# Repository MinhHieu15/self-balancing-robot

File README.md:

# Self-Balancing Robot

Two-wheeled self-balancing robot, built in two versions:

- **v1**: ESP32 + MPU6050 + DC gear motors, MicroPython, PID tuned on the real robot with Ziegler-Nichols.
- **SBR3**: my redesign of the SBR2.1 main board for a stepper-driven robot. ESP32-S3, two A4988 drivers, MPU-9250 IMU, two MAX7219 LED "eyes", 3S LiPo with soft-start, reverse-polarity and surge protection. Designed in Zener/KiCad, checked with DRC, ERC, SPICE and 269 automated board checks.

|  |  |
|---|---|

## Repository layout
```
v1-micropython/
  firmware/main.py           MPU6050, complementary filter, PID, fall detection
  analysis/nichols.py        ultimate period Tu from logged data, Ziegler-Nichols gains
  analysis/data_compare_angle.py   ITAE of the measured angle per 1 s window
  analysis/*.csv, *.xlsx     tilt angle logged on the robot
sbr3/
  kicad/                     schematic and PCB (KiCad 10)
  gerber/, SBR3_gerber_jlcpcb.zip   fabrication files
  SBR3_BOM.csv, BOM_NOTES.md
  docs/                      schematic PDF, copper plots, 3D renders, DRC report, SPICE results
  zener/                     Zener HDL source, SPICE testbenches, board check script and report
  firmware/sbr3_hw_test/     bring-up test for every block on the board
mechanical/                  robot assembly (STEP) and renders
simulation/                  200 Hz balancing simulation, PID vs LQR
docs/                        plots
```

## v1: PID on the real robot
The tilt angle comes from a complementary filter on the accelerometer angle and the integrated gyro rate:

$$\theta_k = \alpha(\theta_{k-1} + \omega\,\Delta t) + (1-\alpha)\,\theta_{acc}, \quad \alpha = 0.98$$

The PID works on the tilt error with a ±0.2° dead band and a clamped integral. The motors stop past 45° or on an I2C error and restart once the robot is upright.

Tuning started from Ziegler-Nichols. Kp was raised until the robot oscillated steadily at Ku = 120; `nichols.py` finds the peaks in the Teleplot log and gives Tu = 0.671 s, so Kp = 72, Ki = 214.5, Kd = 6.04. Final gains after hand tuning: Kp = 120, Ki = 550, Kd = 0.2.

## SBR3 main board
| Block | Parts |
|---|---|
| MCU | ESP32-S3-DevKitC-1 |
| Motors | 2 × A4988, 1/16 microstepping, shared enable |
| IMU | GY-9250 (MPU-9250) on I2C, interrupt line |
| Eyes | 2 × MAX7219 8×8 modules through a 74AHCT125 level shifter |
| Power | XT30, PTC fuse, AO3401A reverse-polarity FET + soft-start FET, SMBJ15A TVS, MP1584EN buck to 5 V, battery voltage divider to ADC |
| UI | buzzer, button, power and status LEDs |

Power-on inrush was 46 A in simulation before the soft-start was added and 0.91 A after. All SPICE results are in [sbr3/docs/spice_results.md](sbr3/docs/spice_results.md); KiCad DRC reports 0 violations and 0 unconnected items, and [the board check report](sbr3/zener/tests/REPORT.md) lists 269 passing checks (netlist match, track widths, clearances, part ratings, fit inside the robot shell).

| Top | Bottom |
|---|---|
|  |  |

`sbr3/firmware/sbr3_hw_test` tests each block from a serial menu (LED, buzzer, button, battery ADC, IMU WHO_AM_I and readings, eye displays, each motor) and prints a PASS/FAIL summary.

## Simulation: PID vs LQR on SBR3
Steppers set wheel acceleration directly, so the model is a wheeled inverted pendulum with wheel acceleration as input. The loop runs at 200 Hz on a complementary-filter angle estimate from a noisy accelerometer and a biased gyro, with one sample of delay and the stepper's acceleration and speed limits. Logs are in `simulation/results/`.

```bash
pip install numpy scipy matplotlib
cd simulation && python balance_sim.py
```

| Scenario | Controller | ITAE | Max tilt | Settling (±1°) | Final position offset |
|---|---|---|---|---|---|
| 10° initial tilt | PID | 0.053 | 10.0° | 0.46 s | 18.6 cm, still drifting |
| 10° initial tilt | LQR | 0.072 | 10.0° | 0.88 s | 6.0 cm |
| Push, +60°/s | PID | 0.061 | 1.2° | 0.04 s | 8.3 cm |
| Push, +60°/s | LQR | 0.081 | 1.3° | 0.46 s | 6.0 cm |

PID brings the angle back faster, but it has no position feedback beyond a weak speed term, so the robot keeps rolling. LQR is slower on the angle and holds position. The remaining 6 cm offset comes from the gyro bias leaking into the angle estimate.

Both controllers barely change up to 20 ms of delay. PID falls at 35 ms; LQR still balances at 40 ms.

The angle estimate is best around α = 0.96–0.98. Lower α lets accelerometer noise through, higher α lets the gyro bias drift in.

## Credits
- **Robot model.** `mechanical/robot_assembly.step` is "Self-Balancing Robot" by [Mr Robonyx](https://grabcad.com/mr.robonyx-1), downloaded from [GrabCAD](https://grabcad.com/library/self-balancing-robot-13) (uploaded 17 February 2025, [video](https://youtu.be/UwOCjUQFoeM)). It is not my design and is included unchanged; the renders in `mechanical/` are made from it with `render_step.py`. Use of the file is subject to the [GrabCAD terms of use](https://grabcad.com/terms).
- **SBR2.1 board.** SBR3 is a redesign of the SBR2.1 main board by H.M. Phan (Robonyx); the SBR3 board was laid out to fit inside the robot model above.

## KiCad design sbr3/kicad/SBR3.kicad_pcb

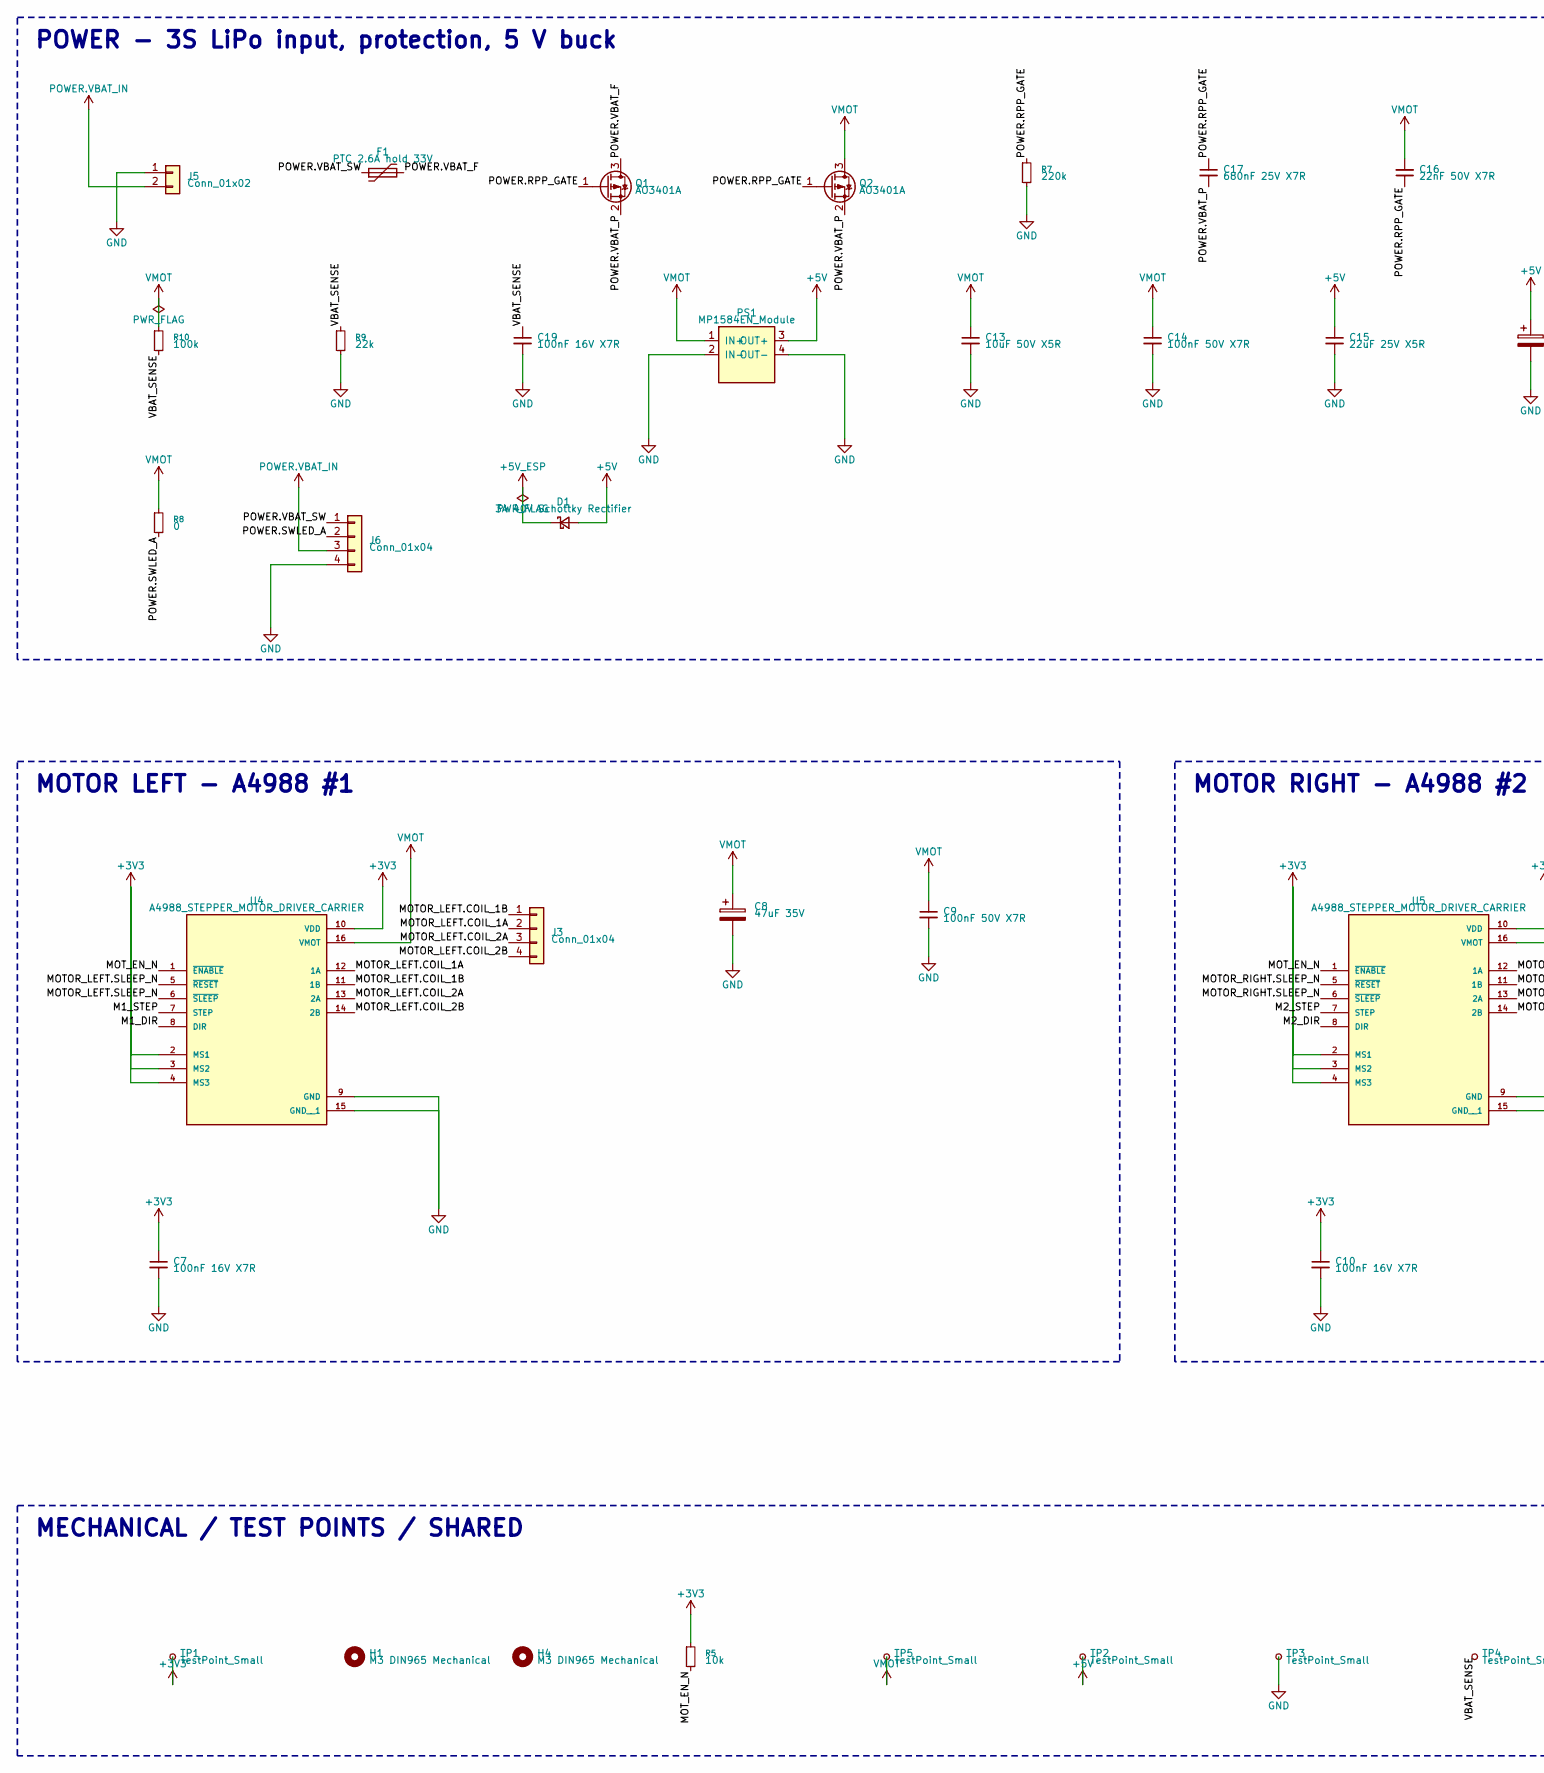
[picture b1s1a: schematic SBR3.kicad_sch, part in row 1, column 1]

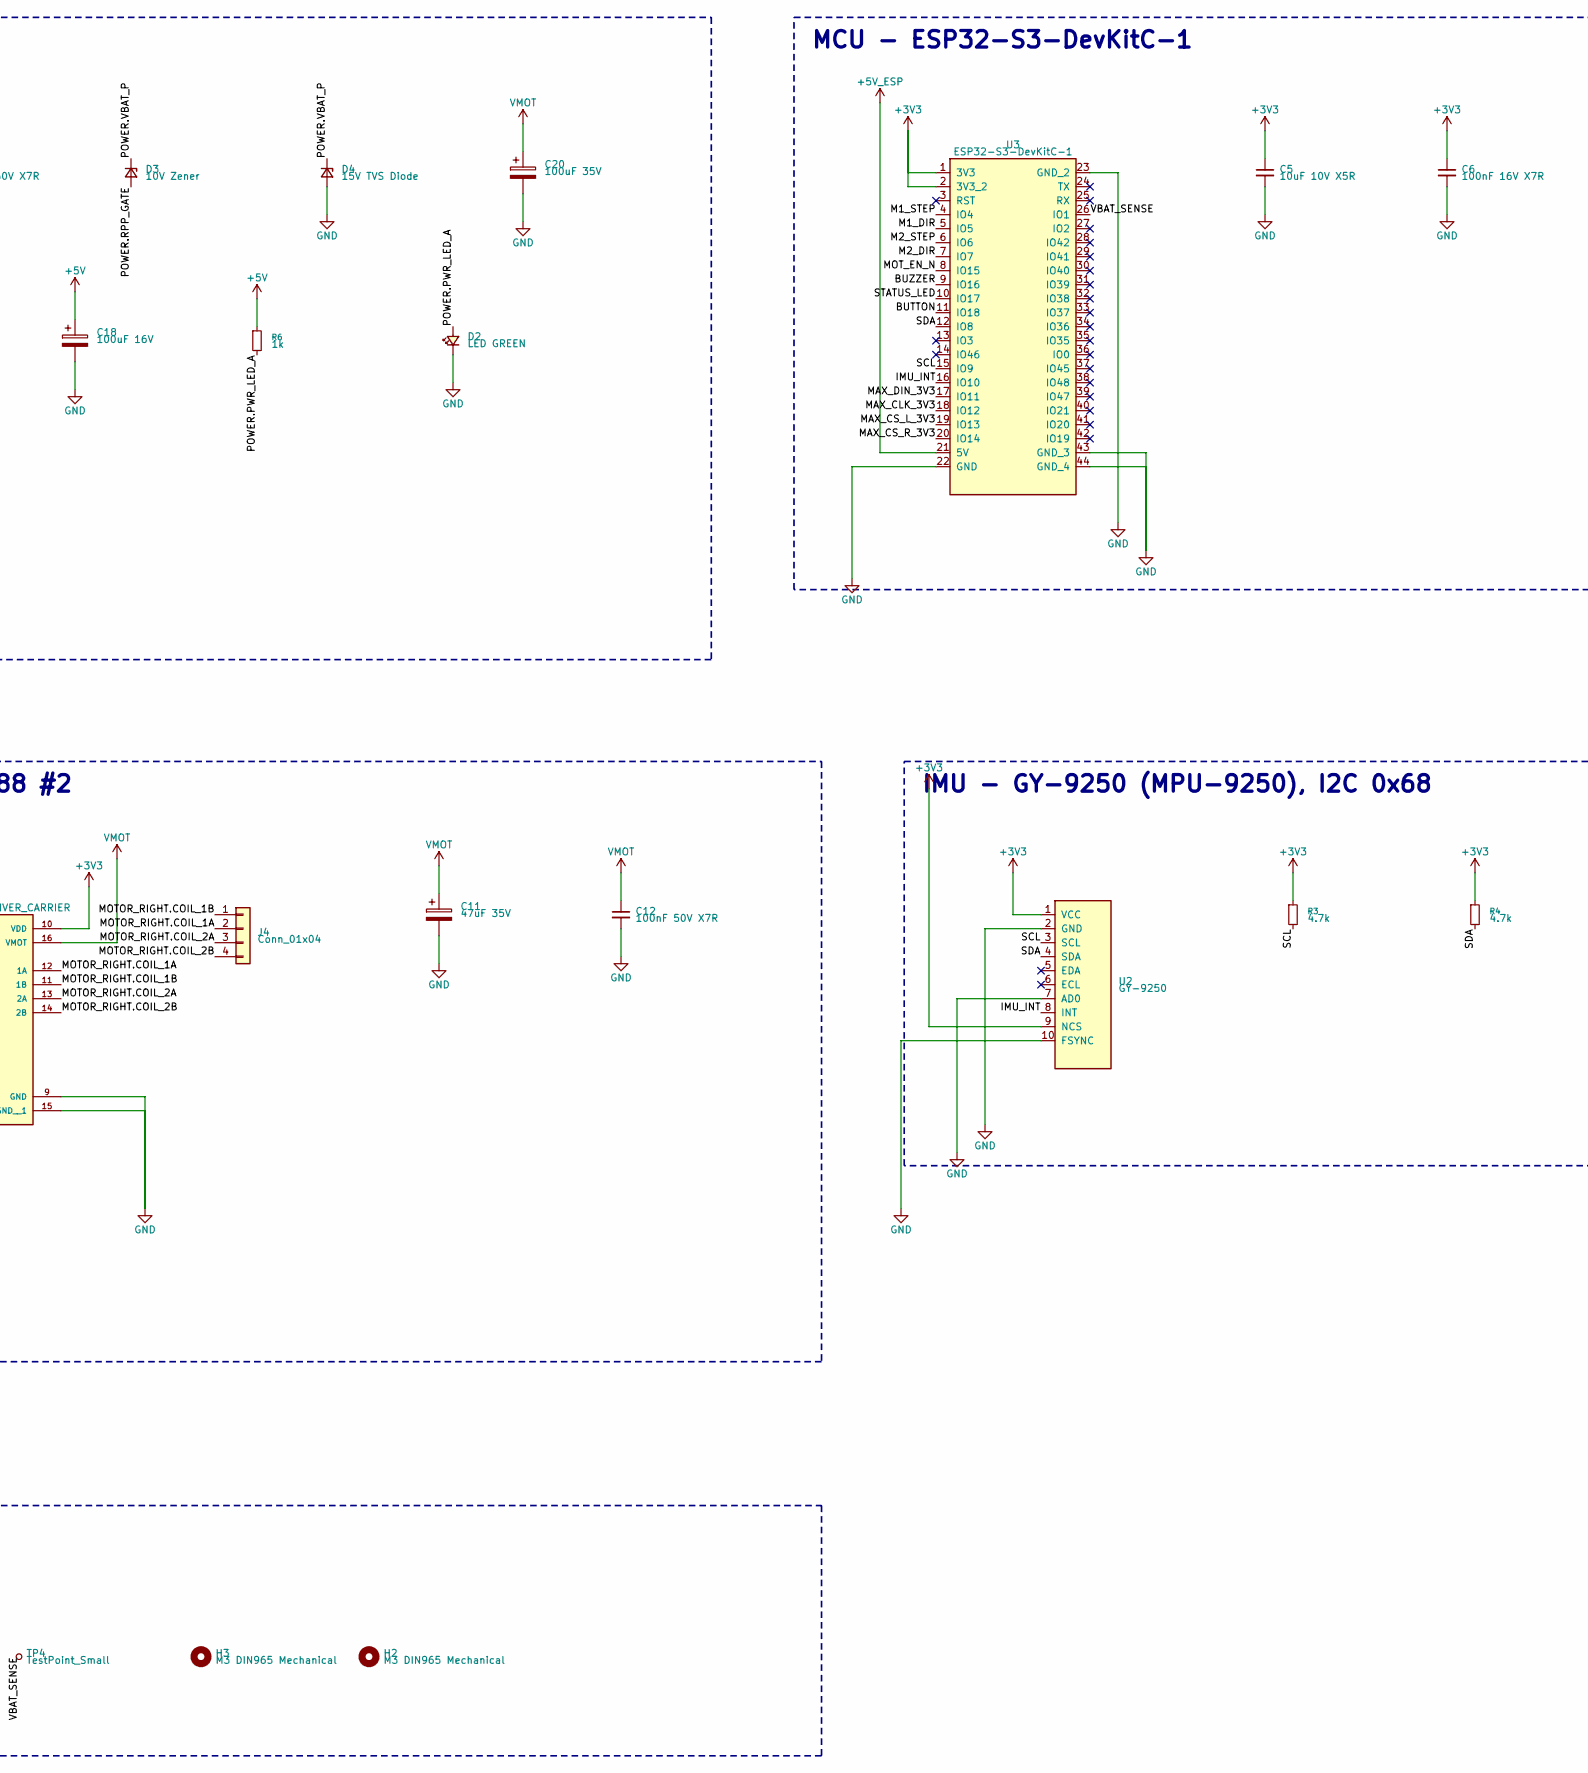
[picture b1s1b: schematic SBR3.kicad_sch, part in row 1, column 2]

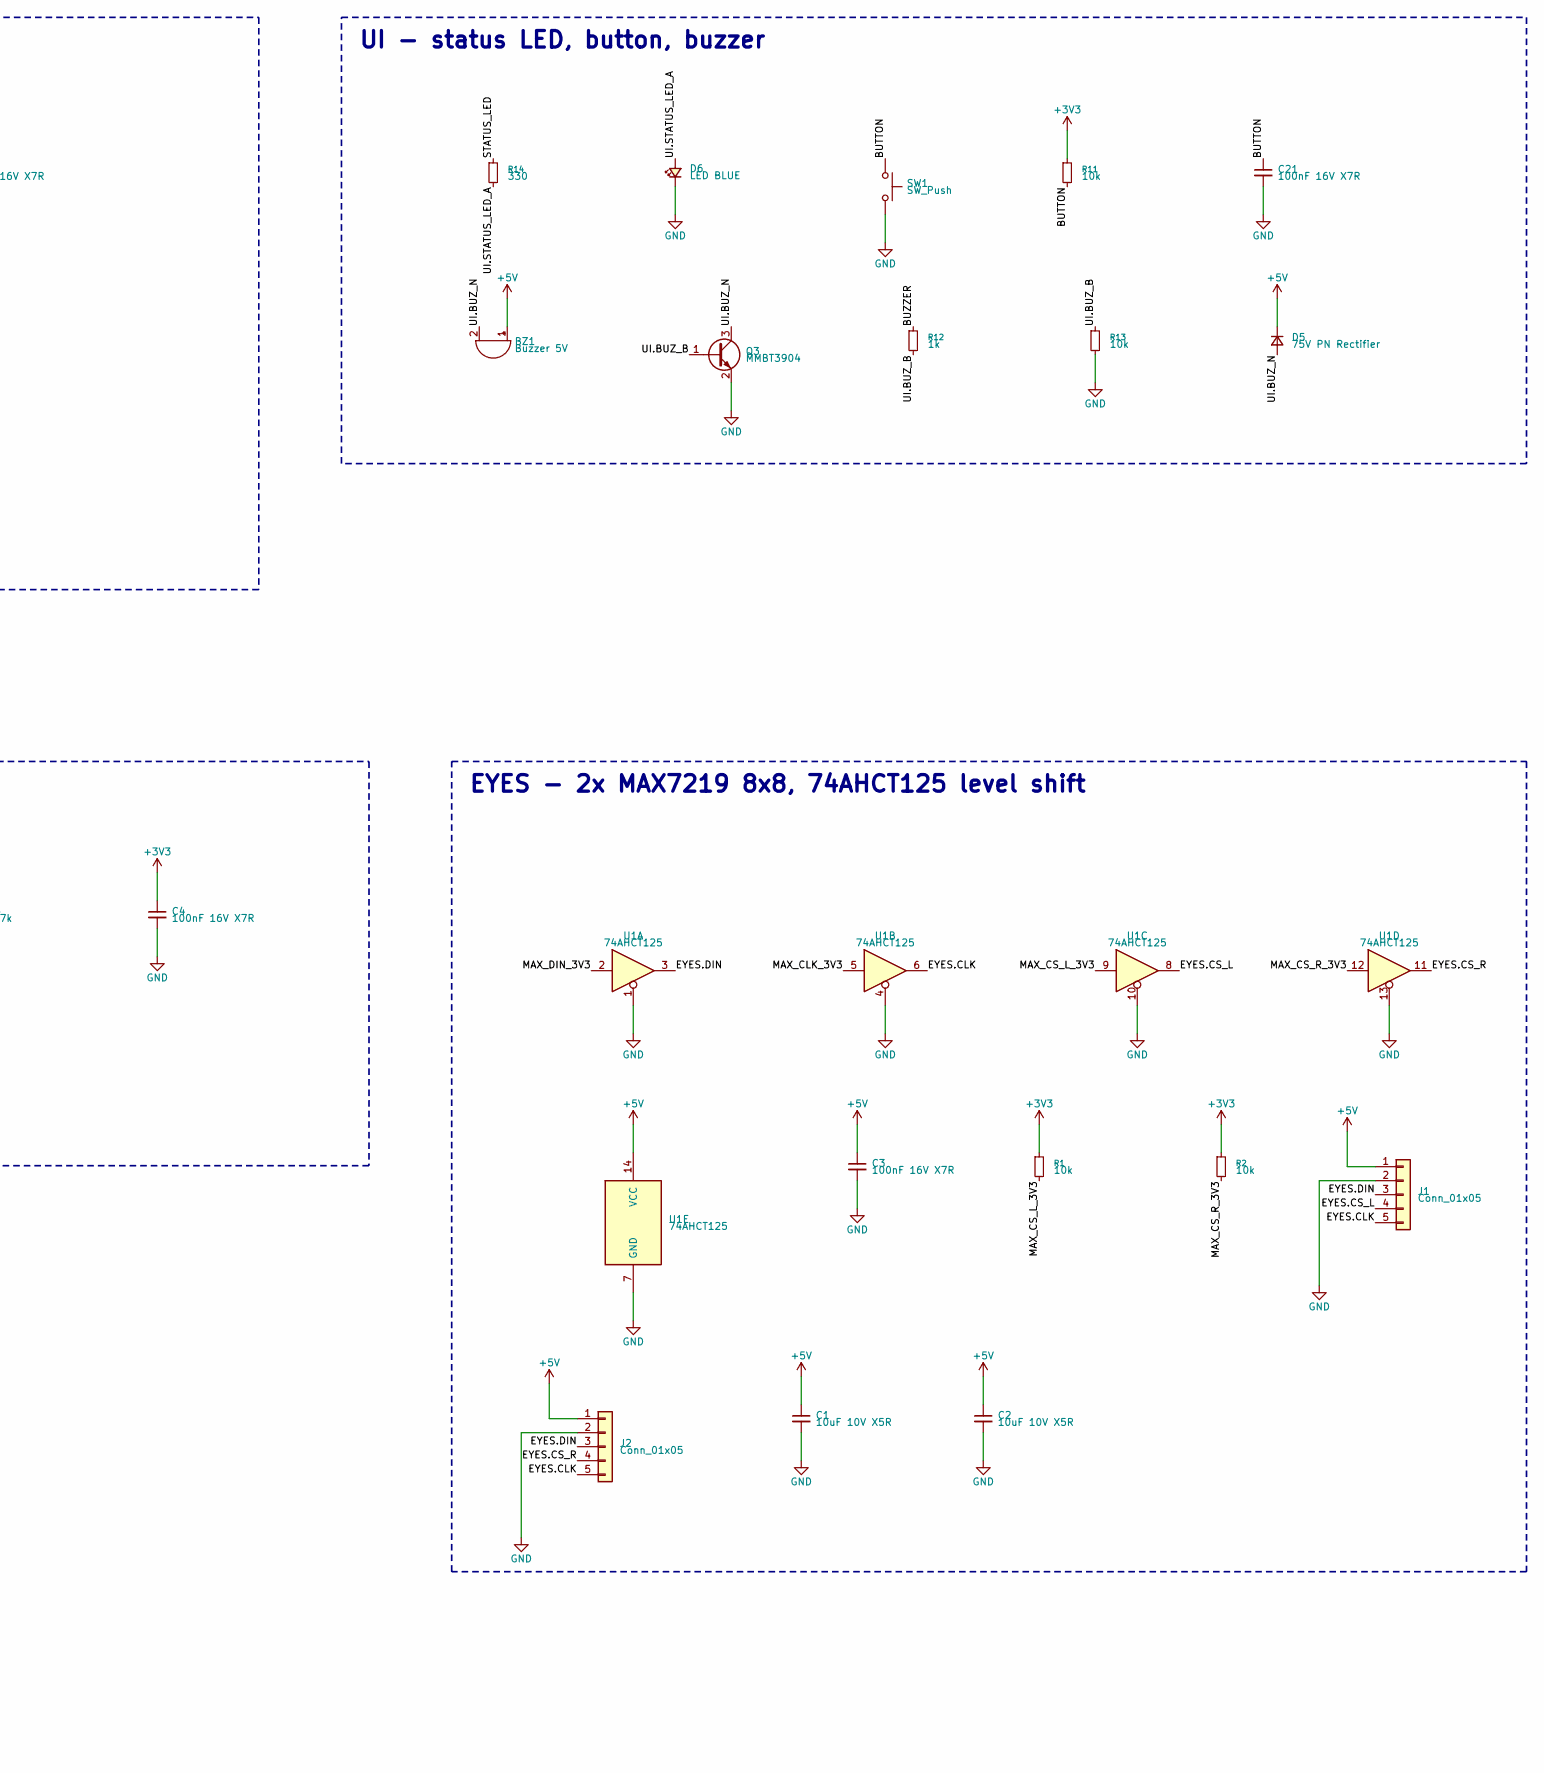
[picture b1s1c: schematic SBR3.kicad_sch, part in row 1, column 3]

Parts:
BZ1: Buzzer 5V; Buzzer_12x9.5RM7.6
C1, C2, C5: 10uF 10V X5R; C_0805_2012Metric
C3, C4, C6, C7, C10, C19, C21: 100nF 16V X7R; C_0805_2012Metric
C8, C11: 47uF 35V; CP_Elec_6.3x5.8
C9, C12, C14: 100nF 50V X7R; C_0805_2012Metric
C13: 10uF 50V X5R; C_1206_3216Metric
C15: 22uF 25V X5R; C_1206_3216Metric
C16: 22nF 50V X7R; C_0805_2012Metric
C17: 680nF 25V X7R; C_0805_2012Metric
C18: 100uF 16V; CP_Elec_6.3x5.8
C20: 100uF 35V; CP_Elec_8x10
D1: 3A 40V Schottky Rectifier; D_SMA
D2: LED GREEN; LED_0805_2012Metric
D3: 10V Zener; D_SOD-123
D4: 15V TVS Diode; D_SMB
D5: 75V PN Rectifier; D_SOD-123
D6: LED BLUE; LED_0805_2012Metric
F1: PTC 2.6A hold 33V; Fuse_2920_7451Metric
H1, H2, H3, H4: M3 DIN965 Mechanical; MountingHole_3.2mm_M3_DIN965
J1, J2: Conn_01x05; PinSocket_1x05_P2.54mm_Vertical
J3, J4, J6: Conn_01x04; JST_XH_B4B-XH-AM_1x04_P2.50mm_Vertical
J5: Conn_01x02; AMASS_XT30U-M_1x02_P5.0mm_Vertical
PS1: MP1584EN_Module; MP1584EN_Module_22x17mm
Q1, Q2: AO3401A; SOT-23
Q3: MMBT3904; SOT-23
R1, R2, R5, R11, R13: 10k; R_0805_2012Metric
R3, R4: 4.7k; R_0805_2012Metric
R6, R12: 1k; R_0805_2012Metric
R7: 220k; R_0805_2012Metric
R8: 0; R_0805_2012Metric
R9: 22k; R_0805_2012Metric
R10: 100k; R_0805_2012Metric
R14: 330; R_0805_2012Metric
SW1: SW_Push; SW_Push_1P1T_XKB_TS-1187A
TP1, TP2, TP3, TP4, TP5: TestPoint_Small; TestPoint_Pad_D1.5mm
U1: 74AHCT125; SOIC-14_3.9x8.7mm_P1.27mm
U2: GY-9250; PinSocket_1x10_P2.54mm_Vertical
U3: ESP32-S3-DevKitC-1
U4, U5: A4988_STEPPER_MOTOR_DRIVER_CARRIER; MODULE_A4988_STEPPER_MOTOR_DRIVER_CARRIER

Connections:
+3V3: C4.1, C5.1, C6.1, C7.1, C10.1, R1.1, R2.1, R3.1, R4.1, R5.1, R11.1, TP1.1, U2.1 (VCC), U2.9 (NCS), U3.1 (3V3), U3.2 (3V3_2), U4.2 (MS1), U4.3 (MS2), U4.4 (MS3), U4.10 (VDD), U5.2 (MS1), U5.3 (MS2), U5.4 (MS3), U5.10 (VDD)
+5V: BZ1.1 (+), C1.1, C2.1, C3.1, C15.1, C18.1, D1.2 (A), D5.1 (K), J1.1, J2.1, PS1.3 (OUT+), R6.1, TP2.1, U1.14 (VCC)
+5V_ESP: D1.1 (K), U3.21 (5V)
BUTTON: C21.1, R11.2, SW1.1, U3.11 (IO18)
BUZZER: R12.1, U3.9 (IO16)
EYES.CLK: J1.5, J2.5, U1.6
EYES.CS_L: J1.4, U1.8
EYES.CS_R: J2.4, U1.11
EYES.DIN: J1.3, J2.3, U1.3
GND: C1.2, C2.2, C3.2, C4.2, C5.2, C6.2, C7.2, C8.2, C9.2, C10.2, C11.2, C12.2, C13.2, C14.2, C15.2, C18.2, C19.2, C20.2, C21.2, D2.1 (K), D4.2 (A), D6.1 (K), J1.2, J2.2, J5.1, J6.4, PS1.2 (IN-), PS1.4 (OUT-), Q3.2 (E), R7.2, R9.2, R13.2, SW1.2, TP3.1, U1.1, U1.4, U1.7 (GND), U1.10, U1.13, U2.2 (GND), U2.7 (AD0), U2.10 (FSYNC), U3.22 (GND), U3.23 (GND_2), U3.43 (GND_3), U3.44 (GND_4), U4.9 (GND), U4.15 (GND__1), U5.9 (GND), U5.15 (GND__1)
IMU.IMU.NC_GY-9250_ECL: U2.6 (ECL)
IMU.IMU.NC_GY-9250_EDA: U2.5 (EDA)
IMU_INT: U2.8 (INT), U3.16 (IO10)
M1_DIR: U3.5 (IO5), U4.8 (DIR)
M1_STEP: U3.4 (IO4), U4.7 (STEP)
M2_DIR: U3.7 (IO7), U5.8 (DIR)
M2_STEP: U3.6 (IO6), U5.7 (STEP)
MAX_CLK_3V3: U1.5, U3.18 (IO12)
MAX_CS_L_3V3: R1.2, U1.9, U3.19 (IO13)
MAX_CS_R_3V3: R2.2, U1.12, U3.20 (IO14)
MAX_DIN_3V3: U1.2, U3.17 (IO11)
MCU.DEVKIT.NC_ESP32-S3-DevKitC-1_IO0: U3.36 (IO0)
MCU.DEVKIT.NC_ESP32-S3-DevKitC-1_IO2: U3.27 (IO2)
MCU.DEVKIT.NC_ESP32-S3-DevKitC-1_IO3: U3.13 (IO3)
MCU.DEVKIT.NC_ESP32-S3-DevKitC-1_IO19: U3.42 (IO19)
MCU.DEVKIT.NC_ESP32-S3-DevKitC-1_IO20: U3.41 (IO20)
MCU.DEVKIT.NC_ESP32-S3-DevKitC-1_IO21: U3.40 (IO21)
MCU.DEVKIT.NC_ESP32-S3-DevKitC-1_IO35: U3.35 (IO35)
MCU.DEVKIT.NC_ESP32-S3-DevKitC-1_IO36: U3.34 (IO36)
MCU.DEVKIT.NC_ESP32-S3-DevKitC-1_IO37: U3.33 (IO37)
MCU.DEVKIT.NC_ESP32-S3-DevKitC-1_IO38: U3.32 (IO38)
MCU.DEVKIT.NC_ESP32-S3-DevKitC-1_IO39: U3.31 (IO39)
MCU.DEVKIT.NC_ESP32-S3-DevKitC-1_IO40: U3.30 (IO40)
MCU.DEVKIT.NC_ESP32-S3-DevKitC-1_IO41: U3.29 (IO41)
MCU.DEVKIT.NC_ESP32-S3-DevKitC-1_IO42: U3.28 (IO42)
MCU.DEVKIT.NC_ESP32-S3-DevKitC-1_IO45: U3.37 (IO45)
MCU.DEVKIT.NC_ESP32-S3-DevKitC-1_IO46: U3.14 (IO46)
MCU.DEVKIT.NC_ESP32-S3-DevKitC-1_IO47: U3.39 (IO47)
MCU.DEVKIT.NC_ESP32-S3-DevKitC-1_IO48: U3.38 (IO48)
MCU.DEVKIT.NC_ESP32-S3-DevKitC-1_RST: U3.3 (RST)
MCU.DEVKIT.NC_ESP32-S3-DevKitC-1_RX: U3.25 (RX)
MCU.DEVKIT.NC_ESP32-S3-DevKitC-1_TX: U3.24 (TX)
MOTOR_LEFT.COIL_1A: J3.2, U4.12 (1A)
MOTOR_LEFT.COIL_1B: J3.1, U4.11 (1B)
MOTOR_LEFT.COIL_2A: J3.3, U4.13 (2A)
MOTOR_LEFT.COIL_2B: J3.4, U4.14 (2B)
MOTOR_LEFT.SLEEP_N: U4.5 (~RESET), U4.6 (~SLEEP)
MOTOR_RIGHT.COIL_1A: J4.2, U5.12 (1A)
MOTOR_RIGHT.COIL_1B: J4.1, U5.11 (1B)
MOTOR_RIGHT.COIL_2A: J4.3, U5.13 (2A)
MOTOR_RIGHT.COIL_2B: J4.4, U5.14 (2B)
MOTOR_RIGHT.SLEEP_N: U5.5 (~RESET), U5.6 (~SLEEP)
MOT_EN_N: R5.2, U3.8 (IO15), U4.1 (~ENABLE), U5.1 (~ENABLE)
POWER.PWR_LED_A: D2.2 (A), R6.2
POWER.RPP_GATE: C16.1, C17.1, D3.2 (A), Q1.1 (G), Q2.1 (G), R7.1
POWER.SWLED_A: J6.2, R8.2
POWER.VBAT_F: F1.2, Q1.3 (D)
POWER.VBAT_IN: J5.2, J6.3
POWER.VBAT_P: C17.2, D3.1 (K), D4.1 (K), Q1.2 (S), Q2.2 (S)
POWER.VBAT_SW: F1.1, J6.1
SCL: R3.2, U2.3 (SCL), U3.15 (IO9)
SDA: R4.2, U2.4 (SDA), U3.12 (IO8)
STATUS_LED: R14.1, U3.10 (IO17)
UI.BUZ_B: Q3.1 (B), R12.2, R13.1
UI.BUZ_N: BZ1.2 (-), D5.2 (A), Q3.3 (C)
UI.STATUS_LED_A: D6.2 (A), R14.2
VBAT_SENSE: C19.1, R9.1, R10.2, TP4.1, U3.26 (IO1)
VMOT: C8.1, C9.1, C11.1, C12.1, C13.1, C14.1, C16.2, C20.1, PS1.1 (IN+), Q2.3 (D), R8.1, R10.1, TP5.1, U4.16 (VMOT), U5.16 (VMOT)

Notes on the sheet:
POWER - 3S LiPo input, protection, 5 V buck
UI - status LED, button, buzzer
MCU - ESP32-S3-DevKitC-1
MOTOR LEFT - A4988 #1
IMU - GY-9250 (MPU-9250), I2C 0x68
EYES - 2x MAX7219 8x8, 74AHCT125 level shift
MECHANICAL / TEST POINTS / SHARED
MOTOR RIGHT - A4988 #2

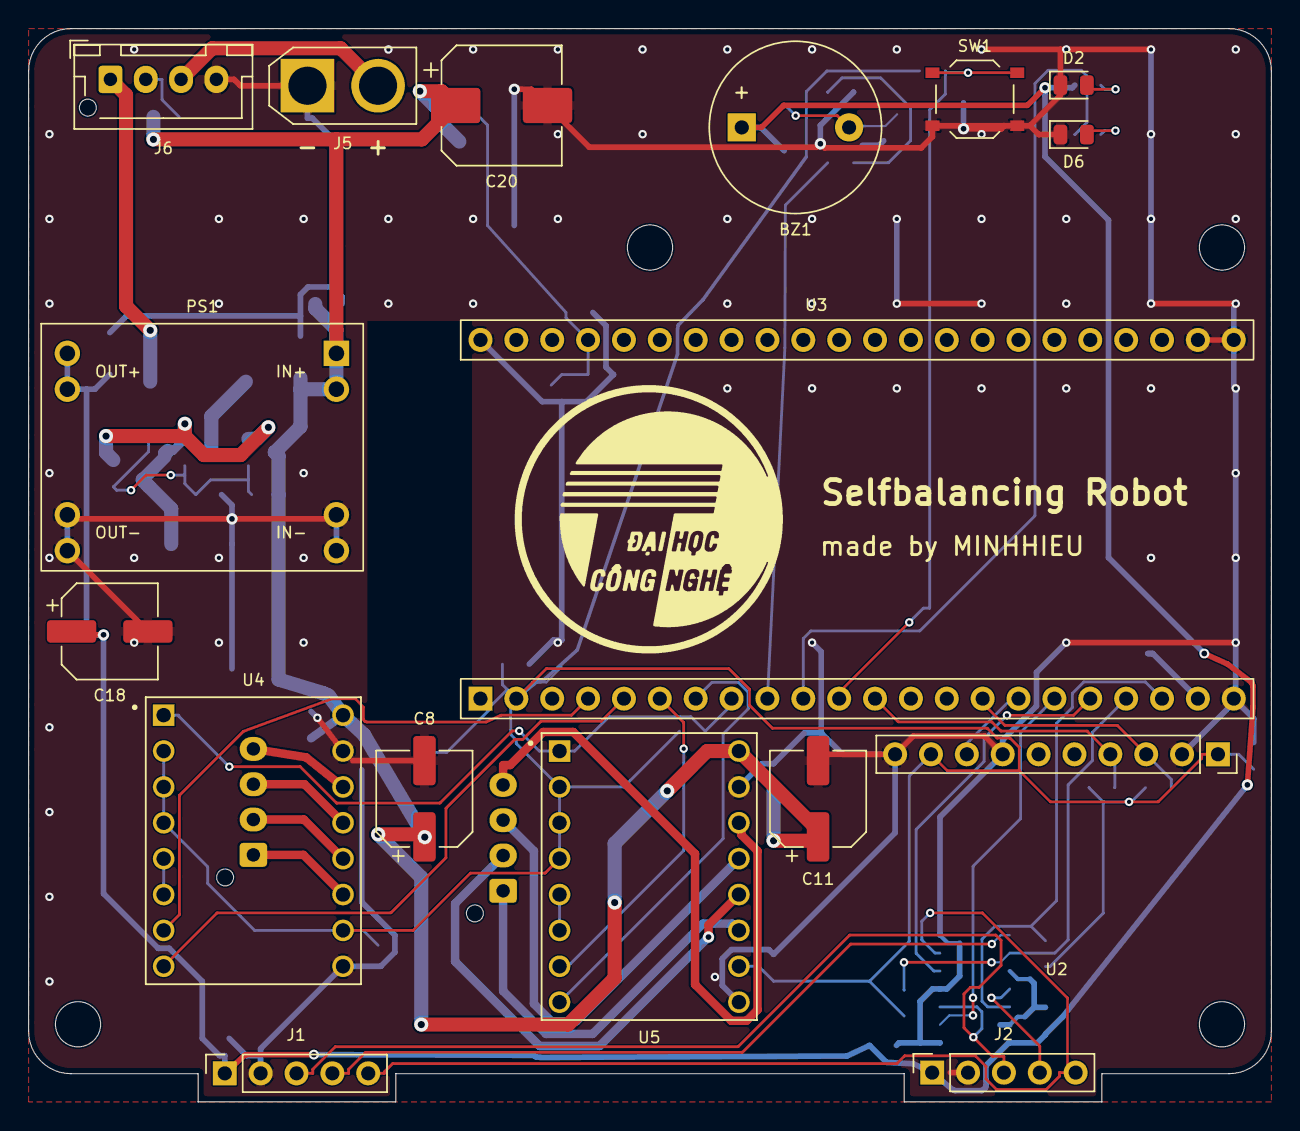
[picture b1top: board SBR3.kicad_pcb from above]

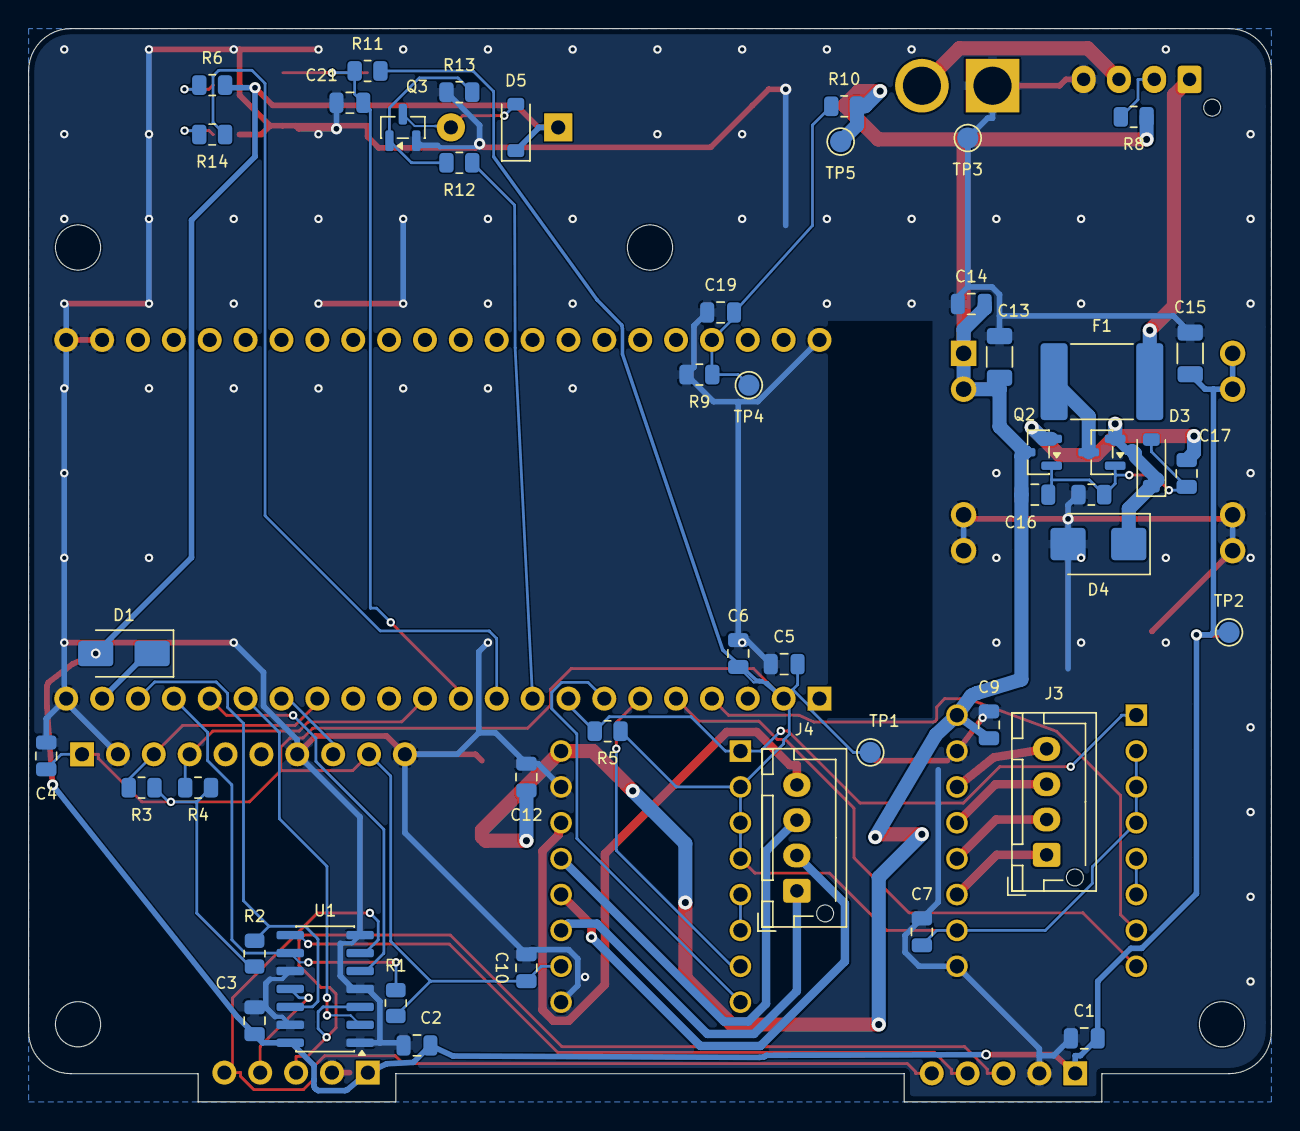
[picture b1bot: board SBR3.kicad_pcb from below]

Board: 2 copper layers, 88.0 x 76.0 mm, 68 parts (47 on the bottom side), 45 nets.

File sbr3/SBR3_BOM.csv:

"Reference","Value","Footprint","Qty"
"BZ1","Buzzer 5V","workspace_components_Buzzer:Buzzer_12x9.5RM7.6","1"
"C1,C2,C5","10uF 10V X5R","stdlib_kicad-footprints_Capacitor_SMD:C_0805_2012Metric","3"
"C3,C4,C6,C7,C10,C19,C21","100nF 16V X7R","stdlib_kicad-footprints_Capacitor_SMD:C_0805_2012Metric","7"
"C8,C11","47uF 35V","workspace_components_CP_47uF_35V:CP_Elec_6.3x5.8","2"
"C9,C12,C14","100nF 50V X7R","stdlib_kicad-footprints_Capacitor_SMD:C_0805_2012Metric","3"
"C13","10uF 50V X5R","stdlib_kicad-footprints_Capacitor_SMD:C_1206_3216Metric","1"
"C15","22uF 25V X5R","stdlib_kicad-footprints_Capacitor_SMD:C_1206_3216Metric","1"
"C16","22nF 50V X7R","stdlib_kicad-footprints_Capacitor_SMD:C_0805_2012Metric","1"
"C17","680nF 25V X7R","stdlib_kicad-footprints_Capacitor_SMD:C_0805_2012Metric","1"
"C18","100uF 16V","workspace_components_CP_100uF_16V:CP_Elec_6.3x5.8","1"
"C20","100uF 35V","workspace_components_CP_100uF_35V:CP_Elec_8x10","1"
"D1","3A 40V Schottky Rectifier","stdlib_kicad-footprints_Diode_SMD:D_SMA","1"
"D2","LED GREEN","stdlib_kicad-footprints_LED_SMD:LED_0805_2012Metric","1"
"D3","10V Zener","stdlib_kicad-footprints_Diode_SMD:D_SOD-123","1"
"D4","15V TVS Diode","stdlib_kicad-footprints_Diode_SMD:D_SMB","1"
"D5","75V PN Rectifier","stdlib_kicad-footprints_Diode_SMD:D_SOD-123","1"
"D6","LED BLUE","stdlib_kicad-footprints_LED_SMD:LED_0805_2012Metric","1"
"F1","PTC 2.6A hold 33V","workspace_components_Polyfuse:Fuse_2920_7451Metric","1"
"J1,J2","Conn_01x05","workspace_components_Conn_01x05:PinSocket_1x05_P2.54mm_Vertical","2"
"J3,J4,J6","Conn_01x04","workspace_components_Conn_01x04:JST_XH_B4B-XH-AM_1x04_P2.50mm_Vertical","3"
"J5","Conn_01x02","workspace_components_Conn_01x02:AMASS_XT30U-M_1x02_P5.0mm_Vertical","1"
"PS1","MP1584EN_Module","workspace_components_MP1584EN_Module:MP1584EN_Module_22x17mm","1"
"Q1,Q2","AO3401A","workspace_components_AO3401A:SOT-23","2"
"Q3","MMBT3904","workspace_components_MMBT3904:SOT-23","1"
"R1,R2,R5,R11,R13","10k","stdlib_kicad-footprints_Resistor_SMD:R_0805_2012Metric","5"
"R3,R4","4.7k","stdlib_kicad-footprints_Resistor_SMD:R_0805_2012Metric","2"
"R6,R12","1k","stdlib_kicad-footprints_Resistor_SMD:R_0805_2012Metric","2"
"R7","220k","stdlib_kicad-footprints_Resistor_SMD:R_0805_2012Metric","1"
"R8","0","stdlib_kicad-footprints_Resistor_SMD:R_0805_2012Metric","1"
"R9","22k","stdlib_kicad-footprints_Resistor_SMD:R_0805_2012Metric","1"
"R10","100k","stdlib_kicad-footprints_Resistor_SMD:R_0805_2012Metric","1"
"R14","330","stdlib_kicad-footprints_Resistor_SMD:R_0805_2012Metric","1"
"SW1","SW_Push","workspace_components_SW_Push:SW_Push_1P1T_XKB_TS-1187A","1"
"U1","74AHCT125","workspace_components_74AHCT125:SOIC-14_3.9x8.7mm_P1.27mm","1"
"U2","GY-9250","workspace_components_GY-9250:PinSocket_1x10_P2.54mm_Vertical","1"
"U3","ESP32-S3-DevKitC-1","workspace_components_ESP32-S3-DevKitC-1:ESP32-S3-DevKitC-1","1"
"U4,U5","A4988_STEPPER_MOTOR_DRIVER_CARRIER","workspace_components_A4988_STEPPER_MOTOR_DRIVER_CARRIER:MODULE_A4988_STEPPER_MOTOR_DRIVER_CARRIER","2"

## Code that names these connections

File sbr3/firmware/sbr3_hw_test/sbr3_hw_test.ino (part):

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#include <Wire.h>

// ---------------------------------------------------------------- SBR3 pin map (schematic modules/Mcu.zen)
constexpr int PIN_M1_STEP = 4;   // MOTOR_LEFT  A4988 STEP
constexpr int PIN_M1_DIR = 5;    // MOTOR_LEFT  A4988 DIR
constexpr int PIN_M2_STEP = 6;   // MOTOR_RIGHT A4988 STEP
constexpr int PIN_M2_DIR = 7;    // MOTOR_RIGHT A4988 DIR
constexpr int PIN_MOT_EN_N = 15; // both A4988 ~ENABLE, pulled high on the board (= disabled)
constexpr int PIN_SDA = 8;
constexpr int PIN_SCL = 9;
constexpr int PIN_IMU_INT = 10;
constexpr int PIN_MAX_DIN = 11;  // 3.3 V side of the 74AHCT125
constexpr int PIN_MAX_CLK = 12;
constexpr int PIN_MAX_CS_L = 13;
constexpr int PIN_MAX_CS_R = 14;
constexpr int PIN_BUZZER = 16;
constexpr int PIN_STATUS_LED = 17;
constexpr int PIN_BUTTON = 18;   // active low, 10k pull-up + 100 nF on the board
constexpr int PIN_VBAT = 1;      // ADC1_CH0, VMOT * 22k / (100k + 22k)

// ---------------------------------------------------------------- hardware constants
constexpr float VBAT_DIVIDER = (100.0f + 22.0f) / 22.0f;
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  }
}
Result results[10];
const char *testNames[10] = {"", "Status LED", "Buzzer", "Button", "Battery ADC", "IMU", "Eyes (MAX7219)",
                             "Left motor", "Right motor", "Both motors"};

// ---------------------------------------------------------------- serial helpers
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Result testStatusLed() {
  Serial.println("\n[1] Status LED (IO17, blue, 330R): blinking 5x");
  for (int i = 0; i < 5; i++) {
    digitalWrite(PIN_STATUS_LED, HIGH);
    delay(200);
    digitalWrite(PIN_STATUS_LED, LOW);
    delay(200);
  }
  return askYesNo("Did the blue status LED blink 5 times?") ? R_PASS : R_FAIL;
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Result testBuzzer() {
  Serial.println("\n[2] Buzzer (IO16 -> MMBT3904, active 5 V buzzer): 3 beeps");
  for (int i = 0; i < 3; i++) {
    digitalWrite(PIN_BUZZER, HIGH);
    delay(120);
    digitalWrite(PIN_BUZZER, LOW);
    delay(200);
  }
  return askYesNo("Did you hear 3 beeps?") ? R_PASS : R_FAIL;
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
  // Interrupt line IMU_INT (IO10): expect ~100 data-ready pulses per second.
  imuIntCount = 0;
  attachInterrupt(digitalPinToInterrupt(PIN_IMU_INT), onImuInt, RISING);
  delay(500);
  detachInterrupt(digitalPinToInterrupt(PIN_IMU_INT));
  uint8_t st;
  i2cRead(MPU_ADDR, 0x3A, &st, 1);
  Serial.printf("  INT pin: %lu pulses in 0.5 s (expected ~50)\n", (unsigned long)imuIntCount);
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}

// ---------------------------------------------------------------- 7-9. stepper motors
void motorsEnable(bool on) { digitalWrite(PIN_MOT_EN_N, on ? LOW : HIGH); }

// Trapezoidal move of one or both motors; steps > 0 forward.
void stepMotors(bool left, bool right, long steps, float maxStepsPerSec) {
  bool fwd = steps > 0;
  steps = labs(steps);
  digitalWrite(PIN_M1_DIR, fwd ? HIGH : LOW);
  digitalWrite(PIN_M2_DIR, fwd ? LOW : HIGH);  // right motor is mirrored on the chassis
  delayMicroseconds(5);
  const float minRate = 400.0f, accel = 8000.0f;  // steps/s, steps/s^2
  float rate = minRate;
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    if (remaining <= stopDist) rate = max(minRate, rate - accel / rate);
    else if (rate < maxStepsPerSec) rate = min(maxStepsPerSec, rate + accel / rate);
    uint32_t half = (uint32_t)(500000.0f / rate);
    if (left) digitalWrite(PIN_M1_STEP, HIGH);
    if (right) digitalWrite(PIN_M2_STEP, HIGH);
    delayMicroseconds(half);
    digitalWrite(PIN_M1_STEP, LOW);
    digitalWrite(PIN_M2_STEP, LOW);
    delayMicroseconds(half);
  }
}
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  delay(300);
  stepMotors(which != 1, which != 0, -STEPS_PER_REV, 3200);
  motorsEnable(false);
  Serial.printf("  VMOT idle %.2f V, while stepping %.2f V (sag %.2f V)\n", vIdle, vLoad, vIdle - vLoad);
  if (vIdle - vLoad > 1.0f) Serial.println("  WARN: large VMOT sag - weak battery, PTC heating or soft-start FET not fully on");
  bool ok = askYesNo(which == 2 ? "Did both wheels turn one revolution forward and back, smoothly?"
                                : "Did that wheel turn one revolution forward and back, smoothly?");
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
void setup() {
  // Motors off first: the board pull-up already holds ~ENABLE high, drive it high as well.
  pinMode(PIN_MOT_EN_N, OUTPUT);
  digitalWrite(PIN_MOT_EN_N, HIGH);
  for (int p : {PIN_M1_STEP, PIN_M1_DIR, PIN_M2_STEP, PIN_M2_DIR, PIN_BUZZER, PIN_STATUS_LED}) {
    pinMode(p, OUTPUT);
    digitalWrite(p, LOW);
  }
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    digitalWrite(p, HIGH);
  }
  pinMode(PIN_BUTTON, INPUT);   // external 10k pull-up
  pinMode(PIN_IMU_INT, INPUT);
  analogSetPinAttenuation(PIN_VBAT, ADC_11db);

  Serial.begin(115200);
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  static uint32_t last = 0;
  if (millis() - last > 1000) {
    last = millis();
    digitalWrite(PIN_STATUS_LED, !digitalRead(PIN_STATUS_LED));
  }
}

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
